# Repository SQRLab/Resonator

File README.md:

# Resonator
Designs, simulations, and control software of the toroidal resonator for the blade trap

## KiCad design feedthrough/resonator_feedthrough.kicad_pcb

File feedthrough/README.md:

Resonator feedthrough with capacitive divider attached

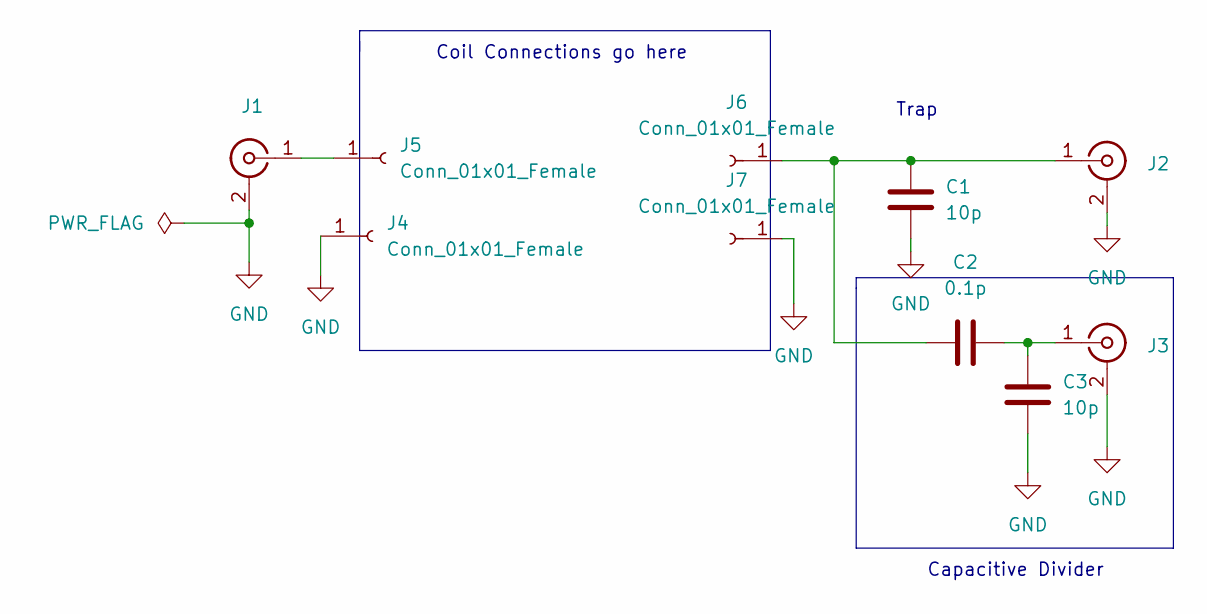
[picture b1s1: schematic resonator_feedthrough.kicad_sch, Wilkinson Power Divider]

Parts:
C1, C3: 10p; R_1206_3216Metric
C2: 0.1p; R_0603_1608Metric
J1, J2, J3: Conn_Coaxial; SMA_Samtec_SMA-J-P-X-ST-EM1_EdgeMount
J4, J5, J6, J7: Conn_01x01_Female

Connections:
GND: C1.1, C3.2, J1.2 (Ext), J2.2 (Ext), J3.2 (Ext), J4.1, J7.1
unnamed: C1.2, C2.1, J2.1 (In), J6.1
unnamed: C2.2, C3.1, J3.1 (In)
unnamed: J1.1 (In), J5.1

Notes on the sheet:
Capacitive Divider
Trap
Coil Connections go here

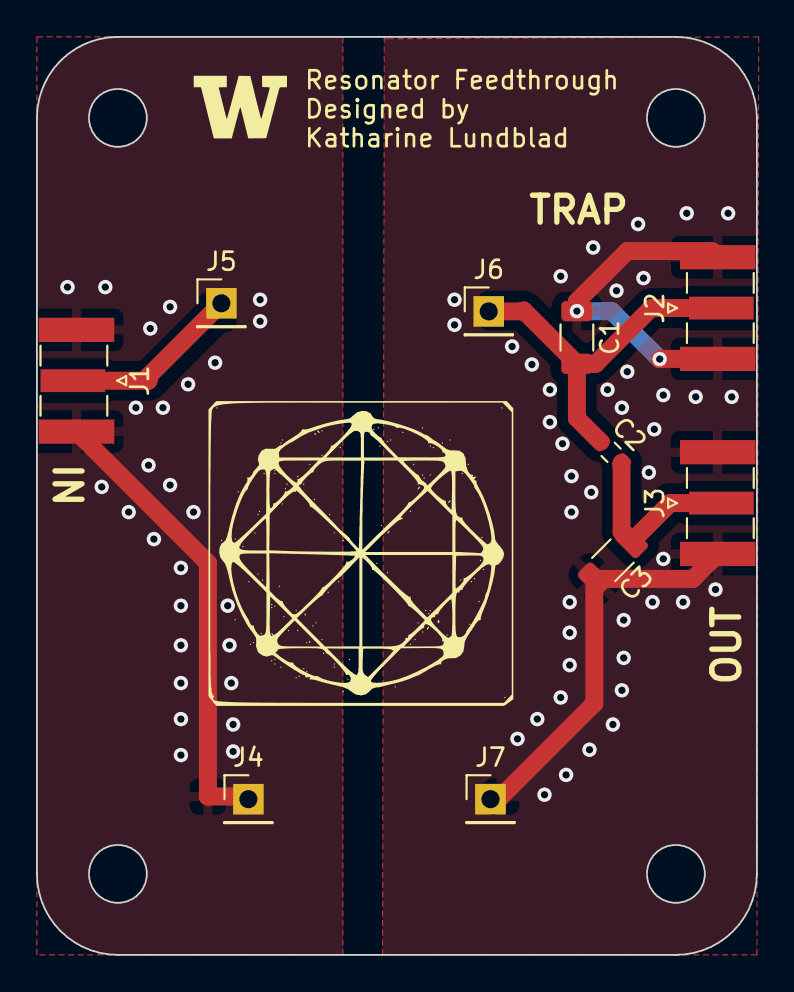
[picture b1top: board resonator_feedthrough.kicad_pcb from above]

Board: 4 copper layers, 40.0 x 51.0 mm, 10 parts (0 on the bottom side), 4 nets.

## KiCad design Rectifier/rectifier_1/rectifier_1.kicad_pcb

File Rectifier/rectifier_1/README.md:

# rectifier_1
These are the designs for a half-wave rectifier on a printed circuit board to convert AC to DC power. For simulations of this circuit, navigate to Resonator/Simulation/LTSpice. This design was created in KiCAD, which is a PCB design software that is free to download here (https://www.kicad.org/download/). In order to view this design, clone this repository and double click the .pro file. This will prompt KiCAD to start and provide a directory to all of the design files. 

### gerber_files
This folder contains the plot and drill files to fabricate the printed circuit board. For most fabrication services, you will need to download this folder as a zip file and upload it to the service's website for ordering. Drill and Plot files are the files that describe the different layers of the board, the routing details, and how to cut the board. 

### rectifier_1-backups
Default folder created by KiCAD to store unsaved backups of the design. 

### uw_logo.pretty
This is a footprint library containing UW and SQRL logos drawn in silkscreen. Silkscreen is the layer of paint that is on top of the board. This is mostly for asthetic, so it is not required to properly view or fabricate the design. If you would like to add the uw_logo.pretty library, go to the "Footprint Editor" and go to "File -> Import Footprint". This will prompt you to upload a footprint from this folder. Save the footprint to a new footprint library or one of the many available ones. Then in the PCB editor, you will be able to "Add Footprint" on the right side-bar and place the footprint on your printed circuit board.  

### rectifier_1.kicad_pcb
This is the pcb file where components are placed and routed. 

### rectifier_1.kicad_pro
This is the main project file containing a directory to all design files and tools in KiCAD.

### rectifier_1.kicad_sch
This is the schematic file containing the circuit diagram and component symbols. 

### Images
This is what the rectifier schematic, PCB, and fabricated render look like respectively

This is what the circuit looks like after fabrication!!

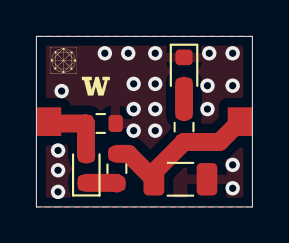
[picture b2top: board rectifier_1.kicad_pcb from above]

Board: 2 copper layers, 12.0 x 9.5 mm, 7 parts (0 on the bottom side), 5 nets.

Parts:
C1: 68p; C_1206_3216Metric
D1, D2: D; D_0603_1608Metric
J1: Conn_Coaxial_x2; SMA-KIT-1.5MF
R1, R2: 5k; R_0603_1608Metric
R3: 2k; R_0603_1608Metric

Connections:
/DC_out: C1.1, J1.2 (IN2), R1.1, R2.1
GND: C1.2, D1.1 (K), J1.3 (EXT), R3.2
unnamed: D1.2 (A), R1.2
unnamed: D2.1 (K), R2.2
unnamed: D2.2 (A), J1.1 (IN1), R3.1

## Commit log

2023-02-02 Added simulation files for feedback portion
2023-02-11 Added design and documentation for half-wave rectifier PCB and fabrication files
2023-02-11 Update README.md
    Added documentation
2023-02-20 Update README.md
    Added pictures
